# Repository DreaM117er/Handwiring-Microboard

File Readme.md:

# Handwiring Microboard 手拉線拓展板

|||
|--|--|
||||

## 詳細說明

在開源鍵盤的世界裡，Pro Micro、Elite-C等是最為常用的開發板，搭載客製化鍵盤很常見的ATMega32U4晶片，其腳位都為12+12 pin的設計。然而開發板本身是不帶螺絲孔位的，因此大部分的鍵盤開發者會將Pro Micro或Elite-C的footprint直接設計在鍵盤的PCB上，再對照韌體使用的Pin腳，連結鍵盤所需的矩陣及元件。

而手拉線拓展板就是為了解決這個問題而設計的，特色如下：

- 支援`正反面`MCU安裝。
- 集中MCU可編程的`18個pin腳`於左右兩側做對稱處理，可左右翻轉做安裝。
- 支援TRRS座`雙面安裝`，可安裝在`4個角落`位置、4個方向。
- 角落有4個`ø3.4mm`的螺絲孔位，可通過`M2`規格的`黃銅銅柱`。

## 使用方式

### A、使用材料

|零件名|數量|備註|
|--|--|--|
|電路板（`PCB`）|1片、2片|一體式、分離式|
|`2pin` 輕觸開關|1個||
|`MCU`|1個、2個|分離式鍵盤需用到2片|
|`TRRS座`|2個|分離式鍵盤用|
|單排排針|`9pin`、`12pin`||
|公母圓排針|`9pin`、`12pin`|推薦|

### B、安裝方式

#### a、一體式

- 首先準備好`PCB`、`MCU`、`2pin輕觸開關`。

- 接著對好MCU上的`腳位`進行焊接安裝。

> **Note**
>
> MCU晶片朝下、朝上都可以安裝在手拉線拓展板上，對好板子上及MCU上的腳位即可。

- 這裡使用`公母圓排針`進行示範安裝。將公圓排針準備好，切正確的大小安裝到MCU上。

- 接著將MCU上的排針焊接完成。

- 再來將`母排針座`安裝到拓展板上。

- 接著從背面焊接固定`母排針座`。

- 再將MCU安裝到拓展板上。

- 接著將`2pin輕觸`開關安裝上去焊接固定。

- 完成後會是這樣的感覺。

> **Note**
>
> 如果你的鍵盤是一體式設計，接著將韌體燒錄進MCU後，就可以使用了。

#### b、分離式

> **Note**
>
> 如果你的鍵盤設計屬分離式，那麼請繼續看下去。

- 接著將已經焊接好MCU的手拉線拓展板跟`TRRS座`準備好。

> **Warning**
>
> TRRS座有4個位置可以安裝選擇，請選一個自己想要的位置安裝。

- 接著將`TRRS座`焊接固定好。

- 焊接好之後翻至`背面`，接著將背面的`跳線ON`的部分焊接起來。

- 跳線焊接好後會是這樣。

> **Warning**
>
> 跳線連接的方式會依照MCU朝上、朝下安裝方式的不同而有差異，務必留意。

- 接著準備好左右邊鍵盤的手拉線拓展板，將韌體燒錄到左右邊，再接上`TRS`/`TRRS線`測試鍵盤即可使用。

## 注意事項

> **Warning**
>
> `MCU`、`TRRS座`、`2pin輕觸開關`務必安裝在`同一側`，以免拓展板失靈。

> **Note**
>
> 拓展板支援`Pro Micro`、`Elite-C`等`12+12 pin`的MCU。

> **Warning**
>
> 如使用`Micro Pico`等`RP2040`等MCU，請依照下表進行`IO pin`的轉換。（以`Sea-Picro`為例）

|Pro Micro||
|--|--|
|Elite-C||
|Sea-Picro||

### IO Pin對照表：

|**Pro Micro、Elite-C左側**|**Pico左側**|**Pro Micro、Elite-C右側**|**Pico右側**|
|--|--|--|--|
|-|`D+`|`VBUS`|`D-`|
|`D3`|`GP0`|`B0`|`RAW`|
|`D2`|`GP1`|`GND`|`GND`|
|`GND`|`GND`|`RST`|`RST`|
|`GND`|`GND`|`VCC`|`3V3`|
|`D1`|`GP2`|`F4`|`GP29`|
|`D0`|`GP3`|`F5`|`GP28`|
|`D4`|`GP4`|`F6`|`GP27`|
|`C6`|`GP5`|`F7`|`GP26`|
|`D7`|`GP6`|`B1`|`GP22`|
|`E6`|`GP7`|`B3`|`GP20`|
|`B4`|`GP8`|`B2`|`GP23`|
|`B5`|`GP9`|`B6`|`GP21`|
|**Elite-C下方**|**Pico下方**|--|--|
|`B7`|`GP12`|--|--|
|`D5`|`GP13`|--|--|
|`C7`|`GP14`|--|--|
|`F1`|`GP15`|--|--|
|`F0`|`GP16`|--|--|

> **Note**
>
> 如鍵盤要將手拉線拓展板設計到鍵盤內，請使用`step檔`進行3D模型的設計。

拓展板規格如下：
- 螺絲孔大小: `ø3.4 mm.`
- 拓展板大小: `34.084 x 47.310 mm`
- 螺絲孔間距: `26.08 mm`, `39.307 mm`

> **Warning**
>
> `TRRS座`預設使用`D2/GP1`進行左右邊鍵盤的資料傳輸，請務必留意。

```
#define SOFT_SERIAL_PIN [D2/GP1]
```

## 參考資料及使用說明

- JLCPCB。
- KiCAD version `7.05`。
- Fusion360。
- `Pro Micro`、`Elite-C`、`Micro Pico`、`Sea Picro`。

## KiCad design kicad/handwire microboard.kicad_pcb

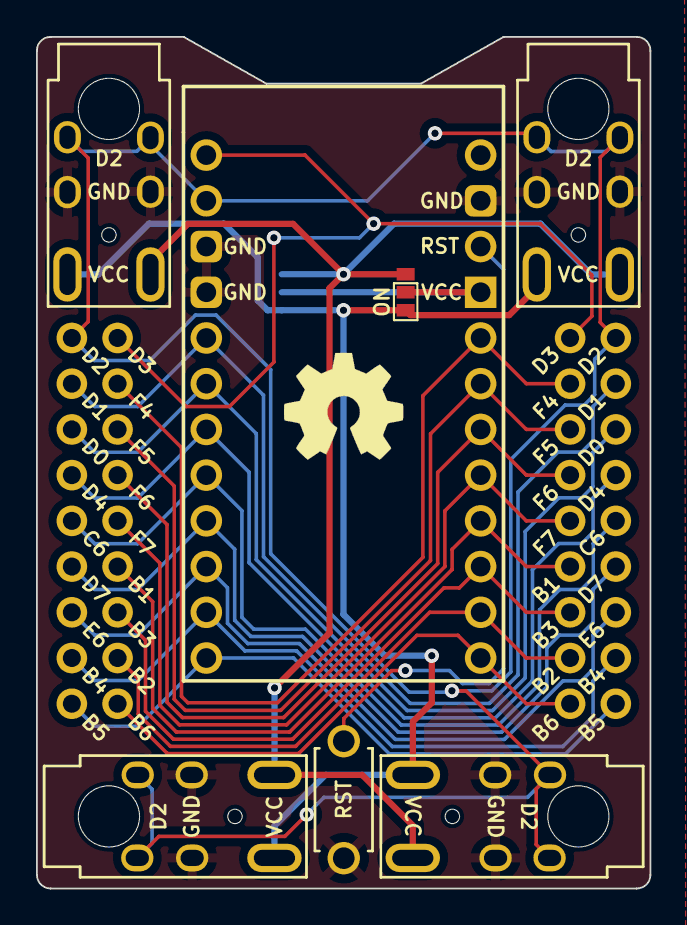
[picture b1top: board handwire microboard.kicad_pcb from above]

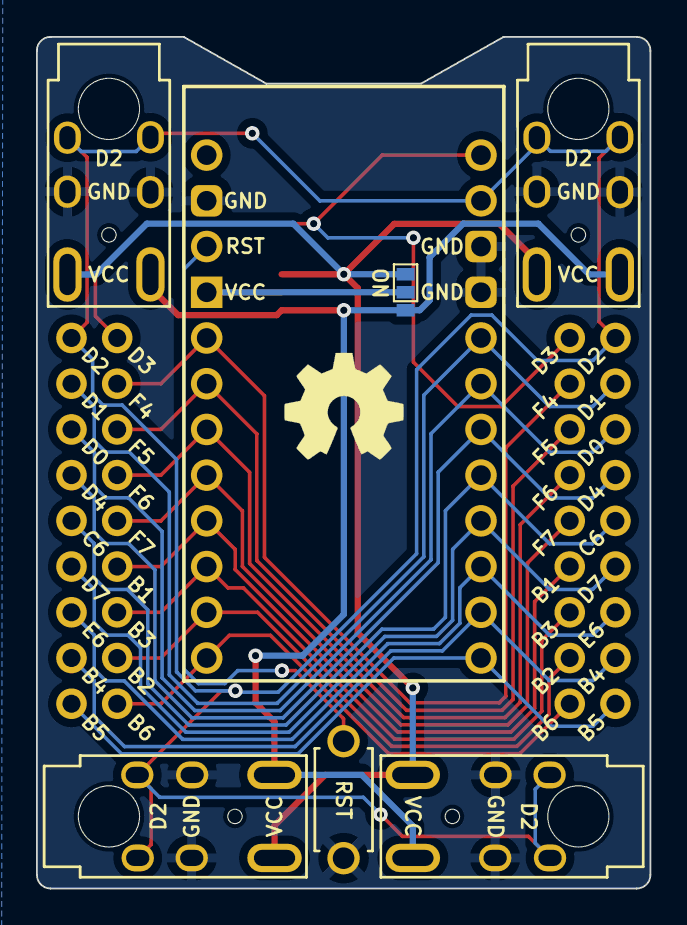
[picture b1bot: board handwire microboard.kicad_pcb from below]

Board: 2 copper layers, 34.1 x 47.3 mm, 10 parts (2 on the bottom side), 23 nets.

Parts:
J1, J2: ProMicro18pin; PinHeader_2x09_P2.54mm_Vertical_Rside
ON: Jumper_Fside; SolderJumper-3_P1.3mm_Open_Pad0.7.x1.0mm_NumberLabels
ON#2: Jumper_Bside; SolderJumper-3_P1.3mm_Open_Pad0.7.x1.0mm_NumberLabels
SW1: SW_Push; ResetSW_1side
T1, T2, T3, T4: AudioJack4; TRRS-PJ-320A, dual side
U1: ProMicro

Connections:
A: ON.1 (A), ON#2.1 (A), T1.1 (T/VCC), T2.1 (T/VCC), T3.1 (T/VCC), T4.1 (T/VCC)
B: ON.3 (B), ON#2.3 (B), T1.4 (S/No), T2.4 (S/No), T3.4 (S/No), T4.4 (S/No)
B1: J1.15, J2.15, U1.16 (22/PB1)
B2: J1.17, J2.17, U1.14 (23/PB2)
B3: J1.16, J2.16, U1.15 (20/PB3)
B4: J1.8, J2.8, U1.11 (8/PB4)
B5: J1.9, J2.9, U1.12 (9/PB5)
B6: J1.18, J2.18, U1.13 (21/PB6)
C6: J1.5, J2.5, U1.8 (5/PC6)
D0: J1.3, J2.3, U1.6 (3/PD0)
D1: J1.2, J2.2, U1.5 (2/PD1)
D2: J1.1, J2.1, T1.2 (R/SNL), T2.2 (R/SNL), T3.2 (R/SNL), T4.2 (R/SNL), U1.2 (1/PD2)
D3: J1.10, J2.10, U1.1 (0/PD3)
D4: J1.4, J2.4, U1.7 (4/PD4)
D7: J1.6, J2.6, U1.9 (6/PD7)
E6: J1.7, J2.7, U1.10 (7/PE6)
F4: J1.11, J2.11, U1.20 (29/PF4)
F5: J1.12, J2.12, U1.19 (28/PF5)
F6: J1.13, J2.13, U1.18 (27/PF6)
F7: J1.14, J2.14, U1.17 (26/PF7)
GND: SW1.1, T1.3 (R/GND), T2.3 (R/GND), T3.3 (R/GND), T4.3 (R/GND), U1.3 (GND), U1.4 (GND), U1.23 (GND)
RESET: SW1.2, U1.22 (RST)
VCC: ON.2 (C), ON#2.2 (C), U1.21 (VCC)

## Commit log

2023-06-14 fixed waring on gbr files
2023-06-14 re-design
2023-06-14 renew readme.md
2023-06-15 fix pcb files
2023-06-15 update size detial
2023-06-20 re-design for board
2023-06-20 update new garber files
2023-06-20 update step file
2023-06-21 fix 80% keyboard pin used
2023-06-21 rename pic
2023-06-22 update gerber files
2023-07-20 re-design for the board
2023-07-20 update new files
2023-08-14 update pcb files
2023-08-19 update new pcb
2023-08-27 fixed issue and update files
2023-08-27 update files
2023-08-28 update new design file
2023-08-28 new design
2023-08-28 update new design
2023-08-28 fixed one track
